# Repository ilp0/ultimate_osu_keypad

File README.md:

# Ultimate osu! keypad

A macropad / mediapad which supports many different layouts. Made specifically to accomodate osu! players who want more than 1u space between their keys. 

4-8 key layout
2 rotary encoders 
Slider potentiometer
8 addressable RGB lights

[Firmware here](https://github.com/ilp0/qmk_firmware)

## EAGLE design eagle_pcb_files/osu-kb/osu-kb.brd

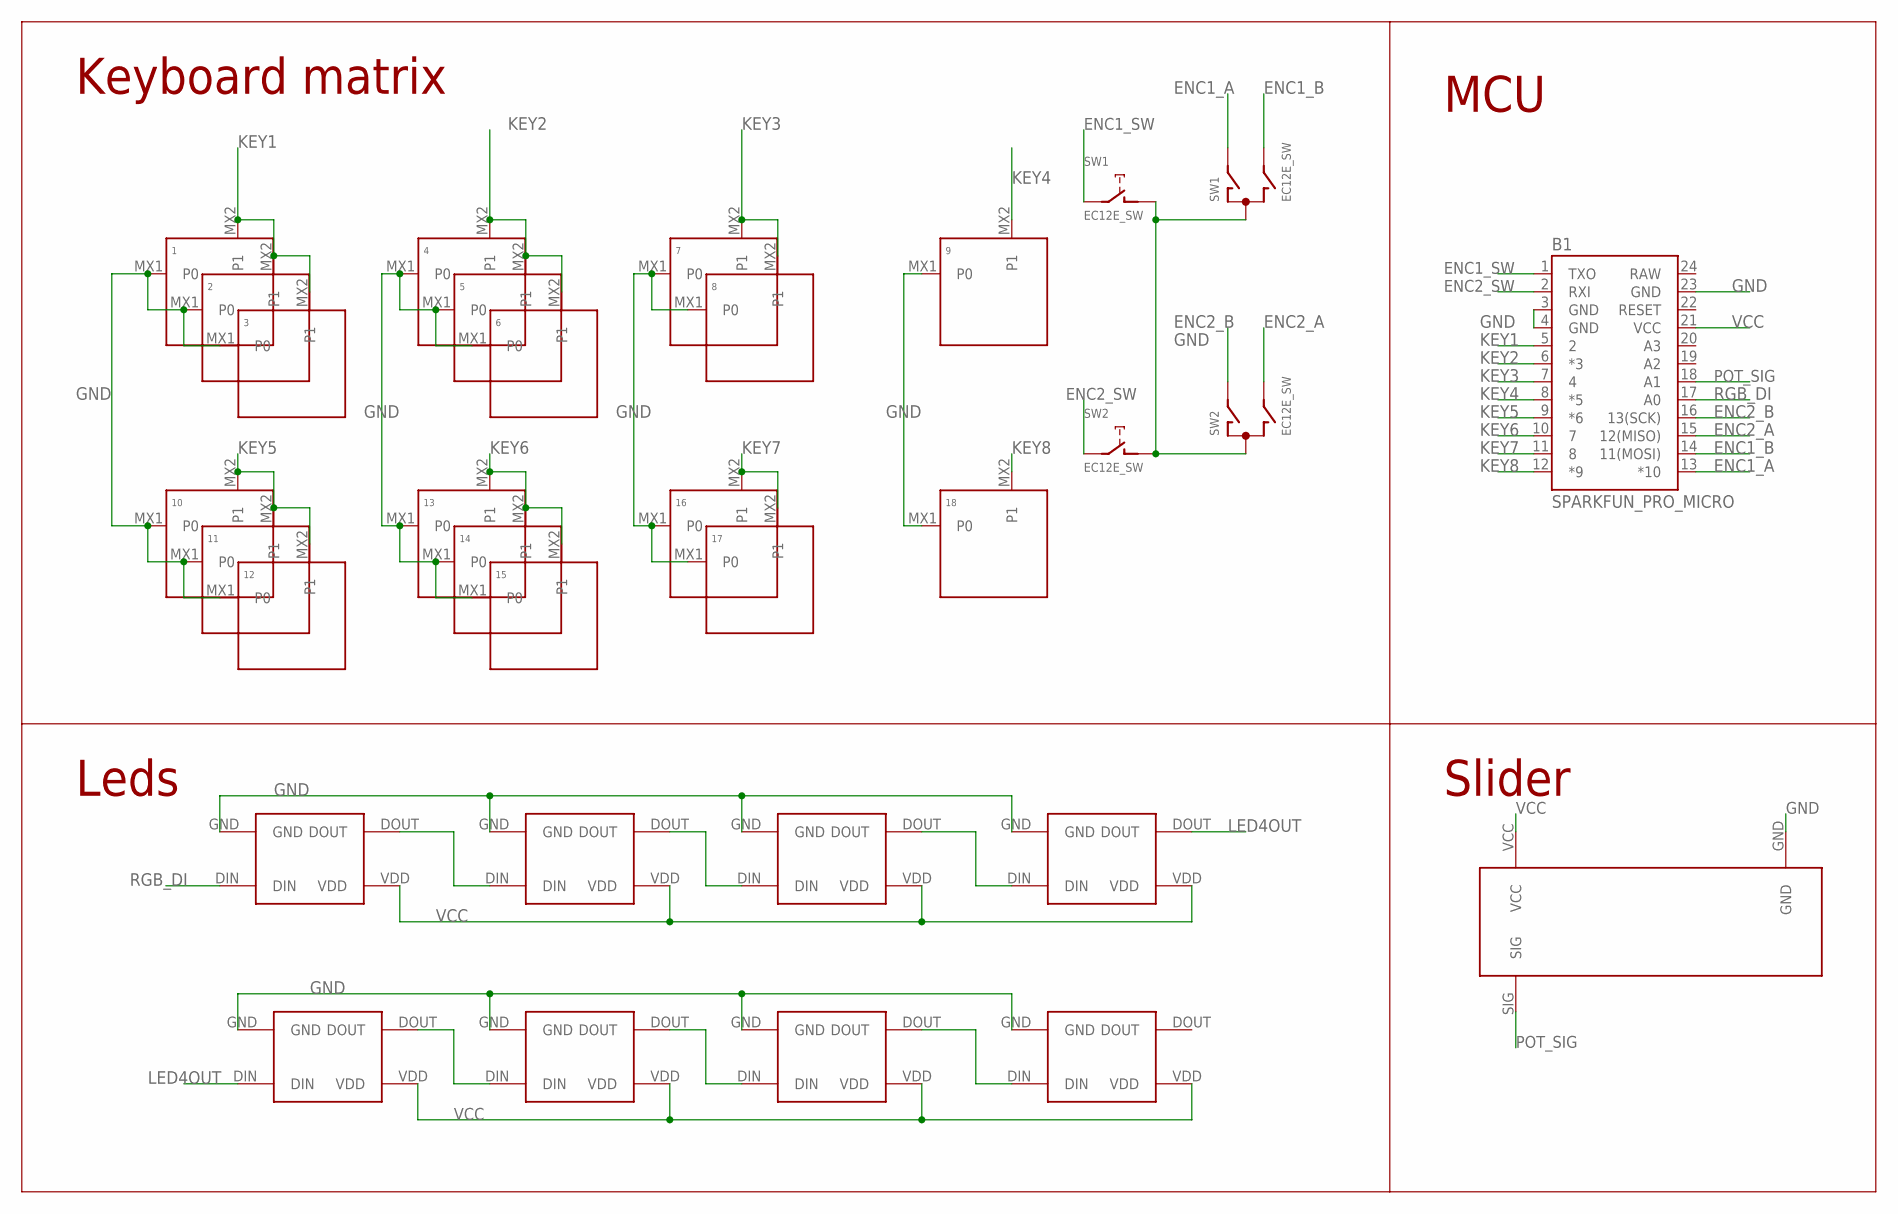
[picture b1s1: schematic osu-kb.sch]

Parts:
1, 2, 3, 4, 5, 6, 7, 8, 9, 10, 11, 12, 13, 14, 15, 16, 17, 18: KEYSWITCH-PLAIN-MX-1U; MX-1U
B1: SPARKFUN_PRO_MICRO
SW1, SW2: EC12E_SW; ALPS_EC12E_SW
U$1, U$2, U$3, U$4, U$5, U$6, U$7, U$8: SK6812MINI-E
U$9: SH_SL60V_B10K

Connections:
ENC1_A: B1.13 (*10), SW1.A
ENC1_B: B1.14 (11(MOSI)), SW1.B
ENC1_SW: B1.1 (TXO), SW1.E (2)
ENC2_A: B1.15 (12(MISO)), SW2.B
ENC2_B: B1.16 (13(SCK)), SW2.A
ENC2_SW: B1.2 (RXI), SW2.E (2)
GND: 1.MX1 (P0), 2.MX1 (P0), 3.MX1 (P0), 4.MX1 (P0), 5.MX1 (P0), 6.MX1 (P0), 7.MX1 (P0), 8.MX1 (P0), 9.MX1 (P0), 10.MX1 (P0), 11.MX1 (P0), 12.MX1 (P0), 13.MX1 (P0), 14.MX1 (P0), 15.MX1 (P0), 16.MX1 (P0), 17.MX1 (P0), 18.MX1 (P0), B1.3 (GND), B1.4 (GND), B1.23 (GND), SW1.C, SW1.D (1), SW2.C, SW2.D (1), U$1.GND, U$2.GND, U$3.GND, U$4.GND, U$5.GND, U$6.GND, U$7.GND, U$8.GND, U$9.GND
KEY1: 1.MX2 (P1), 2.MX2 (P1), 3.MX2 (P1), B1.5 (2)
KEY2: 4.MX2 (P1), 5.MX2 (P1), 6.MX2 (P1), B1.6 (*3)
KEY3: 7.MX2 (P1), 8.MX2 (P1), B1.7 (4)
KEY4: 9.MX2 (P1), B1.8 (*5)
KEY5: 10.MX2 (P1), 11.MX2 (P1), 12.MX2 (P1), B1.9 (*6)
KEY6: 13.MX2 (P1), 14.MX2 (P1), 15.MX2 (P1), B1.10 (7)
KEY7: 16.MX2 (P1), 17.MX2 (P1), B1.11 (8)
KEY8: 18.MX2 (P1), B1.12 (*9)
LED4OUT: U$4.DOUT, U$5.DIN
unnamed: U$1.DOUT, U$2.DIN
unnamed: U$2.DOUT, U$3.DIN
unnamed: U$3.DOUT, U$4.DIN
unnamed: U$5.DOUT, U$6.DIN
unnamed: U$6.DOUT, U$7.DIN
unnamed: U$7.DOUT, U$8.DIN
POT_SIG: B1.18 (A1), U$9.SIG
RAW: B1.24 (RAW)
RGB_DI: B1.17 (A0), U$1.DIN
VCC: B1.21 (VCC), U$1.VDD, U$2.VDD, U$3.VDD, U$4.VDD, U$5.VDD, U$6.VDD, U$7.VDD, U$8.VDD, U$9.VCC

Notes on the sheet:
MCU
Keyboard matrix
Leds
Slider

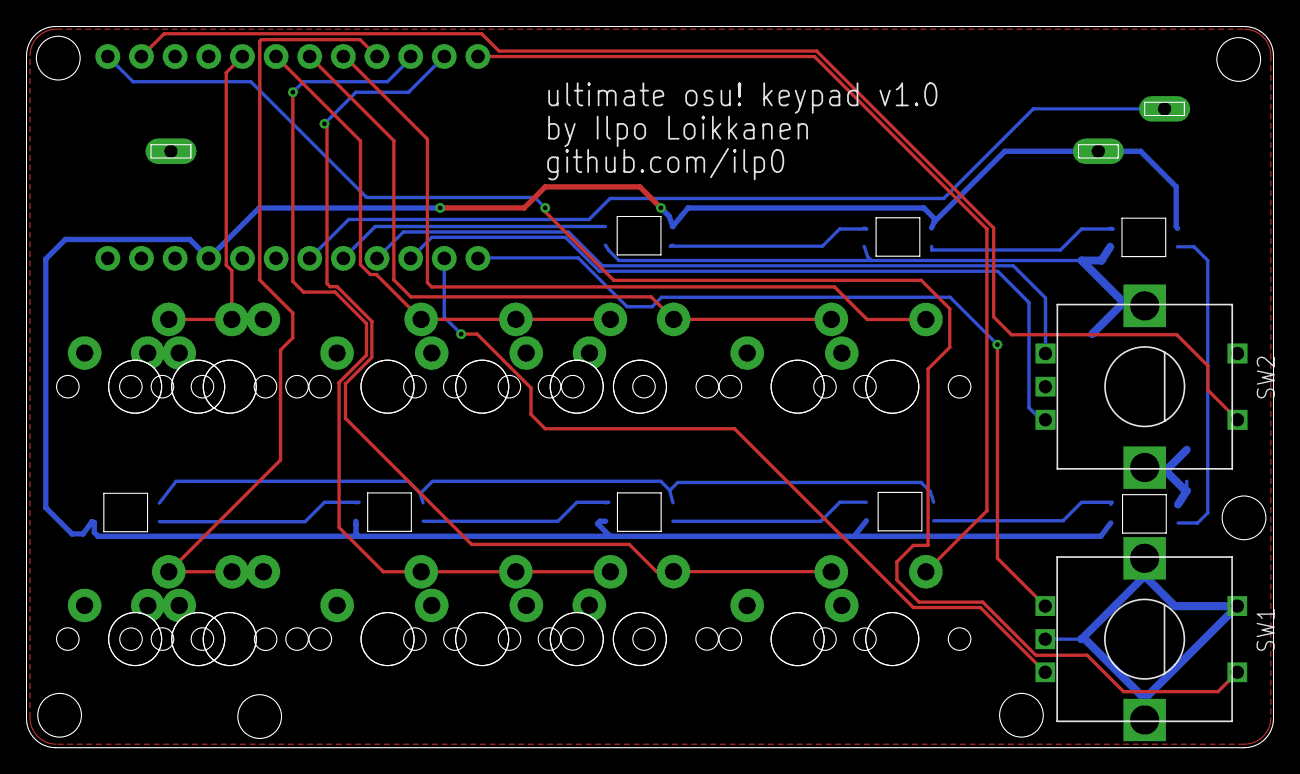
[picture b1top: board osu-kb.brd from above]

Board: 2 copper layers, 94.1 x 54.4 mm, 30 parts (1 on the bottom side), 25 nets.

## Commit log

2021-12-15 Initial commit 2
2021-12-29 add files

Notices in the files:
parts and their libraries:
SparkFun-Boards: Licensing: Creative Commons ShareAlike 4.0 International - https://creativecommons.org/licenses/by-sa/4.0
